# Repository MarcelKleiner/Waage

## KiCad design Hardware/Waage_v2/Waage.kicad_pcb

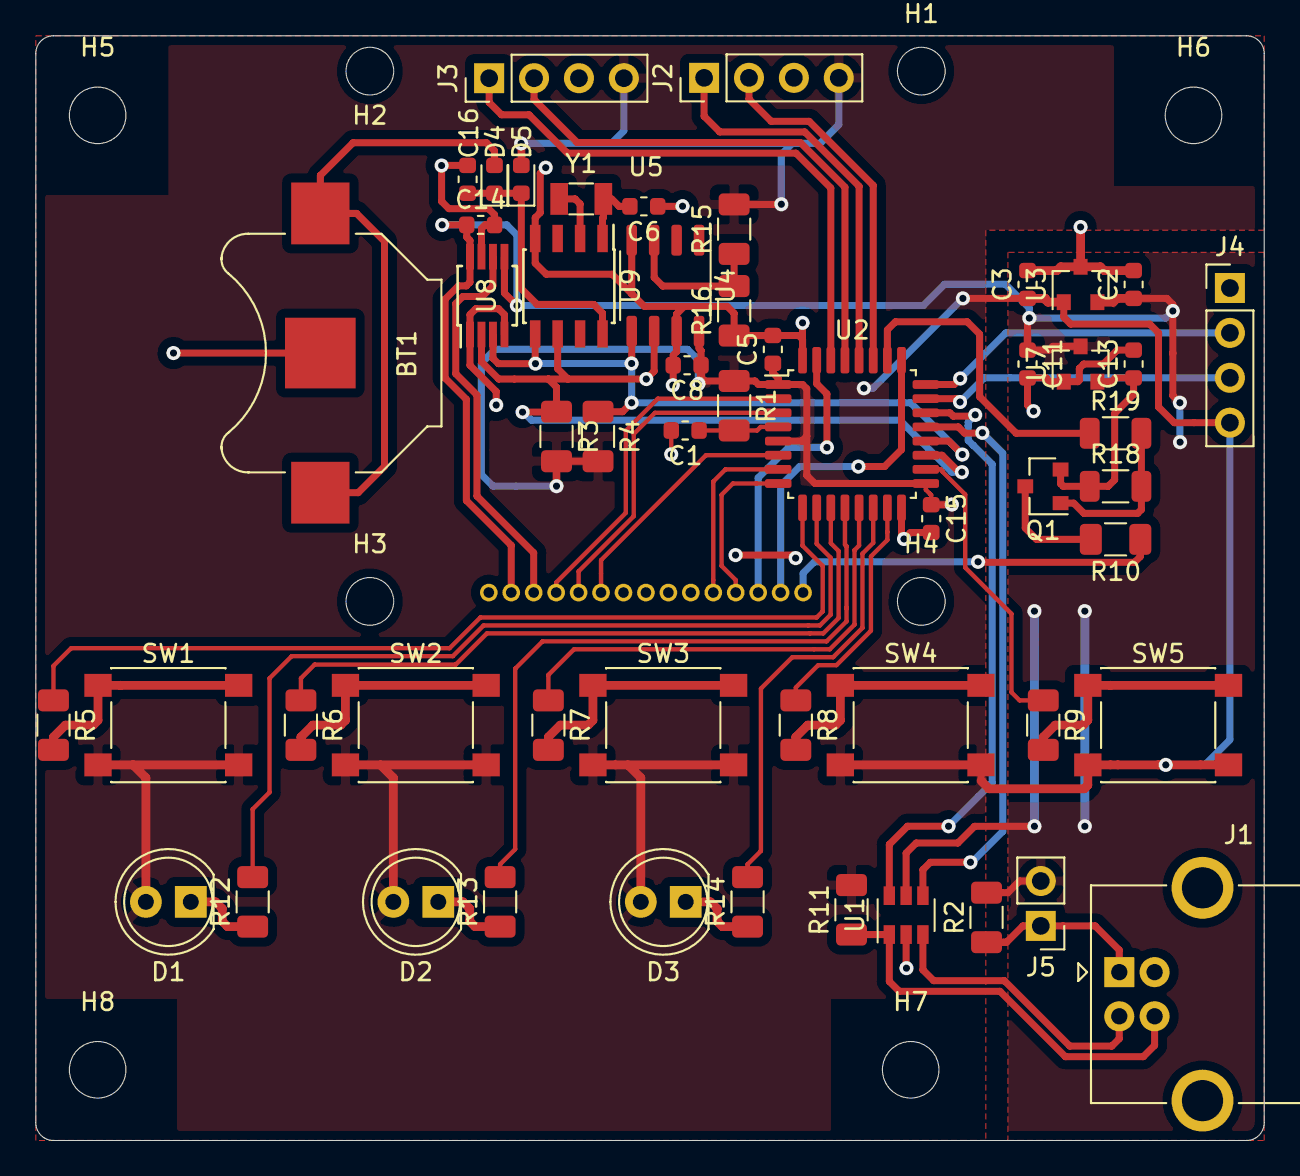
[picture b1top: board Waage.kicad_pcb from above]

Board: 2 copper layers, 69.5 x 62.5 mm, 63 parts (0 on the bottom side), 51 nets.

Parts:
BT1: Battery_Cell; BatteryHolder_Keystone_3000_1x12mm
C1, C5, C6, C8, C14, C15, C16: 100n; C_0603_1608Metric
C2, C3: 2.2u; C_0603_1608Metric
C11, C13: 1u; C_0603_1608Metric
D1, D2, D3: LED; LED_D5.0mm
D4, D5: D_Schottky; D_0603_1608Metric
H1, H2, H3, H4: MountingHole; MountingHole_2.7mm_M2.5_ISO7380
H5, H6, H7, H8: MountingHole; MountingHole_3.2mm_M3_ISO7380
J1: USB_B; USB_B_OST_USB-B1HSxx_Horizontal
J2, J3, J4: Conn_01x04_Female; PinHeader_1x04_P2.54mm_Vertical
J5: Conn_01x02_Female; PinHeader_1x02_P2.54mm_Vertical
Q1: BC856; SOT-23
R1: 100k; R_1206_3216Metric
R2: 0; R_1206_3216Metric
R3, R4: 4.7K; R_1206_3216Metric
R5, R6, R7, R8, R9, R11, R15, R16, R19: 1.5k; R_1206_3216Metric
R10: 120; R_1206_3216Metric
R12, R13, R14: 240; R_1206_3216Metric
R18: 10k; R_1206_3216Metric
SW1, SW2, SW3, SW4, SW5: SW_Push; SW_SPST_PTS645
U1: USBLC6-2SC6; SOT-23-6
U2: STM32L412K8Tx; LQFP-32_7x7mm_P0.8mm
U3: MCP1812BT_033TT; SOT-23
U4: M24M02-DWMN3TP/K; SO-8_3.9x4.9mm_P1.27mm
U5: NHD-0212WH
U7: MCP1700-35022E_SOT23; SOT-23
U8: MCP4541T; MSOP-8_3x3mm_P0.65mm
U9: PCF8563T; SOIC-8_3.9x4.9mm_P1.27mm
Y1: Crystal; Crystal_SMD_3215-2Pin_3.2x1.5mm

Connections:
3.5V: Q1.3, R10.2
+3V3: C3.1, C5.1, C8.1, C15.1, D1.2, D2.2, D3.2, D5.2, J2.4, J3.4, J4.4, R1.1, R3.2, R4.2, R11.2, R15.2, SW1.2, SW2.2, SW3.2, SW4.2, SW5.2, U2.1, U2.5, U2.17, U3.1, U4.8
D+: J1.3, R11.1, U1.1
D-: J1.2, U1.3
DATA_L1: J2.2, U2.27
DATA_L2: J3.2, U2.29
DB0: U2.7, U5.11
DB1: U2.8, U5.12
DB2: U2.31, U5.13
DB3: U2.25, U5.14
DM: U1.4, U2.21
DP: U1.6, U2.22
GND: BT1.2, C1.2, C2.2, C3.2, C5.2, C6.1, C8.2, C11.2, C13.2, C14.2, C15.2, C16.2, J1.4, J1.5, J2.3, J3.3, J4.1, R16.1, U1.2, U2.16, U2.32, U3.3, U4.4, U4.7, U5.1, U7.1, U8.1, U8.4, U8.7, U9.4
KONTRAST: U5.3, U8.6
LCD_E: U2.6, U5.6
LCD_LIGHT: R19.1, U2.26
LCD_RS: U2.2, U5.4
LCD_RW: U2.3, U5.5
LED_BW: R12.2, U2.10
LED_PW: R13.2, U2.12
LED_SUM: R14.2, U2.14
unnamed: BT1.1, D4.2
unnamed: C1.1, R1.2, U2.4
unnamed: C6.2, U9.1, Y1.1
unnamed: C13.1, Q1.2, R18.1, U7.2
unnamed: C16.1, D4.1, D5.1, U9.8
unnamed: D1.1, R12.1
unnamed: D2.1, R13.1
unnamed: D3.1, R14.1
unnamed: J1.1, J5.1, R2.1
unnamed: Q1.1, R18.2, R19.2
unnamed: R5.2, SW1.1
unnamed: R6.2, SW2.1
unnamed: R7.2, SW3.1
unnamed: R8.2, SW4.1
unnamed: R9.2, SW5.1
unnamed: R10.1, U5.15
unnamed: R15.1, R16.2, U4.3
unnamed: U9.2, Y1.2
SCK_L1: J2.1, U2.28
SCK_L2: J3.1, U2.30
SCL: R3.1, U2.19, U4.6, U8.2, U9.6
SDA: R4.1, U2.20, U4.5, U8.3, U9.5
SWCLK: J4.2, U2.24
SWDIO: J4.3, U2.23
SW_BW: R5.1, U2.9
SW_PW: R6.1, U2.11
SW_SUM: R7.1, U2.13
SW_TAR: R9.1, U2.18
SW_TOTAL: R8.1, U2.15
VBUS: C2.1, C11.1, C14.1, J5.2, R2.2, U1.5, U3.2, U5.2, U7.3, U8.5, U8.8

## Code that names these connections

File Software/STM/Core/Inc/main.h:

/* USER CODE BEGIN Header */
/**
  ******************************************************************************
  * @file           : main.h
  * @brief          : Header for main.c file.
  *                   This file contains the common defines of the application.
  ******************************************************************************
  * @attention
  *
  * <h2><center>&copy; Copyright (c) 2020 STMicroelectronics.
  * All rights reserved.</center></h2>
  *
  * This software component is licensed by ST under BSD 3-Clause license,
  * the "License"; You may not use this file except in compliance with the
  * License. You may obtain a copy of the License at:
  *                        opensource.org/licenses/BSD-3-Clause
  *
  ******************************************************************************
  */
/* USER CODE END Header */

/* Define to prevent recursive inclusion -------------------------------------*/
#ifndef __MAIN_H
#define __MAIN_H

#ifdef __cplusplus
extern "C" {
#endif

/* Includes ------------------------------------------------------------------*/
#include "stm32l4xx_hal.h"

/* Private includes ----------------------------------------------------------*/
/* USER CODE BEGIN Includes */

/* USER CODE END Includes */

/* Exported types ------------------------------------------------------------*/
/* USER CODE BEGIN ET */

/* USER CODE END ET */

/* Exported constants --------------------------------------------------------*/
/* USER CODE BEGIN EC */

/* USER CODE END EC */

/* Exported macro ------------------------------------------------------------*/
/* USER CODE BEGIN EM */
void USBReceive(uint8_t *buf);
/* USER CODE END EM */

/* Exported functions prototypes ---------------------------------------------*/
void Error_Handler(void);

/* USER CODE BEGIN EFP */

/* USER CODE END EFP */

/* Private defines -----------------------------------------------------------*/
#define LCD_RS_Pin GPIO_PIN_14
#define LCD_RS_GPIO_Port GPIOC
#define LCD_RW_Pin GPIO_PIN_15
#define LCD_RW_GPIO_Port GPIOC
#define LCD_E_Pin GPIO_PIN_0
#define LCD_E_GPIO_Port GPIOA
#define DB0_Pin GPIO_PIN_1
#define DB0_GPIO_Port GPIOA
#define DB1_Pin GPIO_PIN_2
#define DB1_GPIO_Port GPIOA
#define SW_BW_Pin GPIO_PIN_3
#define SW_BW_GPIO_Port GPIOA
#define LED_BW_Pin GPIO_PIN_4
#define LED_BW_GPIO_Port GPIOA
#define SW_PW_Pin GPIO_PIN_5
#define SW_PW_GPIO_Port GPIOA
#define LED_PW_Pin GPIO_PIN_6
#define LED_PW_GPIO_Port GPIOA
#define SW_SUM_Pin GPIO_PIN_7
#define SW_SUM_GPIO_Port GPIOA
#define LED_SUM_Pin GPIO_PIN_0
#define LED_SUM_GPIO_Port GPIOB
#define SW_TOTAL_Pin GPIO_PIN_1
#define SW_TOTAL_GPIO_Port GPIOB
#define SW_TAR_Pin GPIO_PIN_8
#define SW_TAR_GPIO_Port GPIOA
#define DB3_Pin GPIO_PIN_15
#define DB3_GPIO_Port GPIOA
#define LCD_LIGHT_Pin GPIO_PIN_3
#define LCD_LIGHT_GPIO_Port GPIOB
#define DATA_L1_Pin GPIO_PIN_4
#define DATA_L1_GPIO_Port GPIOB
#define CLK_L1_Pin GPIO_PIN_5
#define CLK_L1_GPIO_Port GPIOB
#define DATA_L2_Pin GPIO_PIN_6
#define DATA_L2_GPIO_Port GPIOB
#define CLK_L2_Pin GPIO_PIN_7
#define CLK_L2_GPIO_Port GPIOB
#define DB2_Pin GPIO_PIN_3
#define DB2_GPIO_Port GPIOH
/* USER CODE BEGIN Private defines */

/* USER CODE END Private defines */

#ifdef __cplusplus
}
#endif

#endif /* __MAIN_H */

/************************ (C) COPYRIGHT STMicroelectronics *****END OF FILE****/

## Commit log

2020-10-04 Update Layout + CAD
2020-10-04 update CAD + Layout
2020-10-09 update layout
2020-10-11 update Software
2020-10-11 Update STM Software
2020-10-11 add LoadCell and timer
2020-10-14 ADD LAYOUT V2
2020-10-17 update software stm
2020-10-17 no message
2020-10-23 HW ueberarbeitung
2020-10-23 update hw
2020-11-10 update log book reader
2020-11-10 update exefile
2020-11-10 bin update
2021-11-17 bug fix
2021-11-18 workbranche update
2021-11-18 update UI
2021-11-18 irgen ein scheiss
